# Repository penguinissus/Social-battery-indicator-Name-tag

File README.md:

# Social battery indicator Name tag

Schematic Screenshot:  
  
PCB Screenshot:  
  
3D View:  

# Description
I took the idea of making a name tag and added lights as a social battery indicator  
The three lights will be red yellow and green respectively  
The 18 transistors are supposed to be 3 SR flip flops and 3 or gates  
Heres a logic diagram  

# Bill of Materials  
1 Battery Holder  
3 LEDs  
3 Push Buttons  
6 PNP Transistors  
12 NPN Transistors  
1 10k Resistor  
9 1k Resistors  
3 220 Resistors  
  
Slack username: @penguinissus

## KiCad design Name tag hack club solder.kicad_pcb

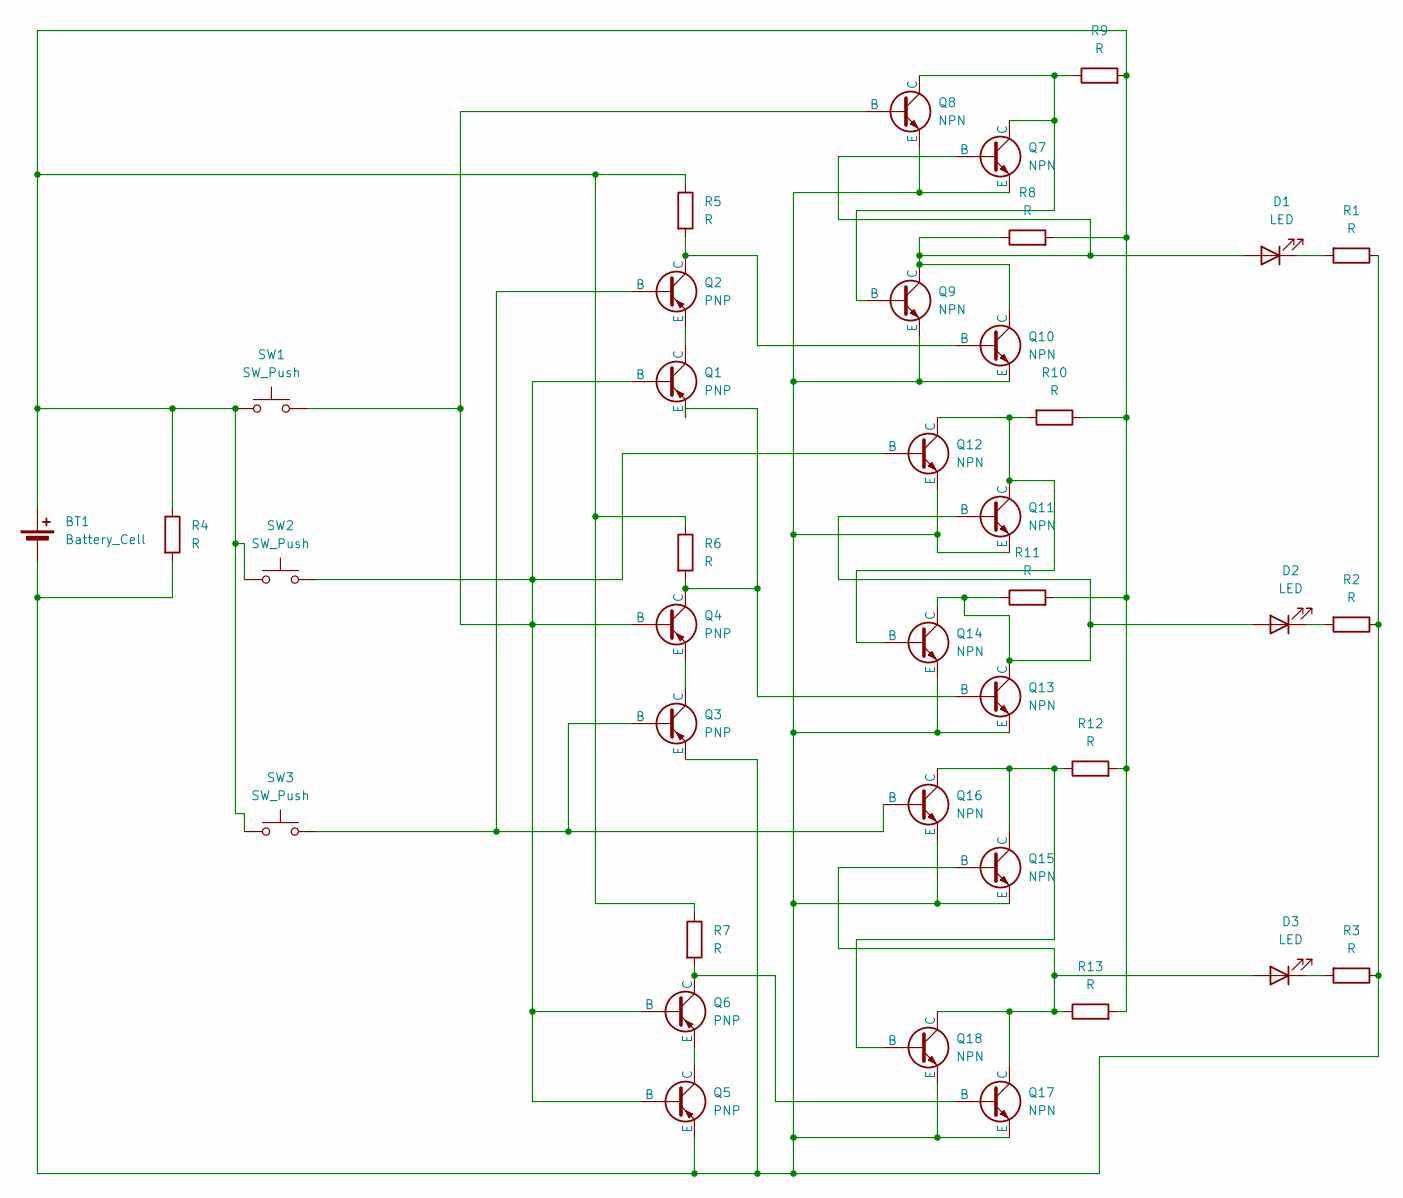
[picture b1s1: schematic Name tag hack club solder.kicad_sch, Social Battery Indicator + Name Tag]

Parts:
BT1: Battery_Cell; BatteryHolder_Keystone_3034_1x20mm
D1, D2, D3: LED; LED_D5.0mm
Q1, Q2, Q3, Q4, Q5, Q6: PNP; TO-92L_HandSolder
Q7, Q8, Q9, Q10, Q11, Q12, Q13, Q14, Q15, Q16, Q17, Q18: NPN; TO-92L_HandSolder
R1, R2, R3, R4, R5, R6, R7, R8, R9, R10, R11, R12, R13: R; R_Axial_DIN0207_L6.3mm_D2.5mm_P7.62mm_Horizontal
SW1, SW2, SW3: SW_Push; SW_PUSH_6mm

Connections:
unnamed: BT1.1 (+), R4.1, R5.1, R6.1, R7.1, R8.2, R9.2, R10.1, R11.2, R12.2, R13.2, SW1.1, SW2.1, SW3.1
unnamed: BT1.2 (-), Q3.3 (E), Q5.3 (E), Q7.3 (E), Q8.3 (E), Q9.3 (E), Q10.3 (E), Q11.3 (E), Q12.3 (E), Q13.3 (E), Q14.3 (E), Q15.3 (E), Q16.3 (E), Q17.3 (E), Q18.3 (E), R1.1, R2.1, R3.1, R4.2
unnamed: D1.2 (A), Q7.2 (B), Q9.1 (C), Q10.1 (C), R8.1
unnamed: D1.1 (K), R1.2
unnamed: D2.2 (A), Q11.2 (B), Q13.1 (C), Q14.1 (C), R11.1
unnamed: D2.1 (K), R2.2
unnamed: D3.2 (A), Q15.2 (B), Q17.1 (C), Q18.1 (C), R13.1
unnamed: D3.1 (K), R3.2
unnamed: Q1.2 (B), Q4.2 (B), Q5.2 (B), Q6.2 (B), Q8.2 (B), Q12.2 (B), SW1.2, SW2.2
unnamed: Q1.1 (C), Q2.3 (E)
unnamed: Q1.3 (E), Q4.1 (C), Q13.2 (B), R6.2
unnamed: Q3.1 (C), Q4.3 (E)
unnamed: Q5.1 (C), Q6.3 (E)
unnamed: Q7.1 (C), Q8.1 (C), Q9.2 (B), R9.1
unnamed: Q2.1 (C), Q10.2 (B), R5.2
unnamed: Q11.1 (C), Q12.1 (C), Q14.2 (B), R10.2
unnamed: Q15.1 (C), Q16.1 (C), Q18.2 (B), R12.1
unnamed: Q2.2 (B), Q3.2 (B), Q16.2 (B), SW3.2
unnamed: Q6.1 (C), Q17.2 (B), R7.2

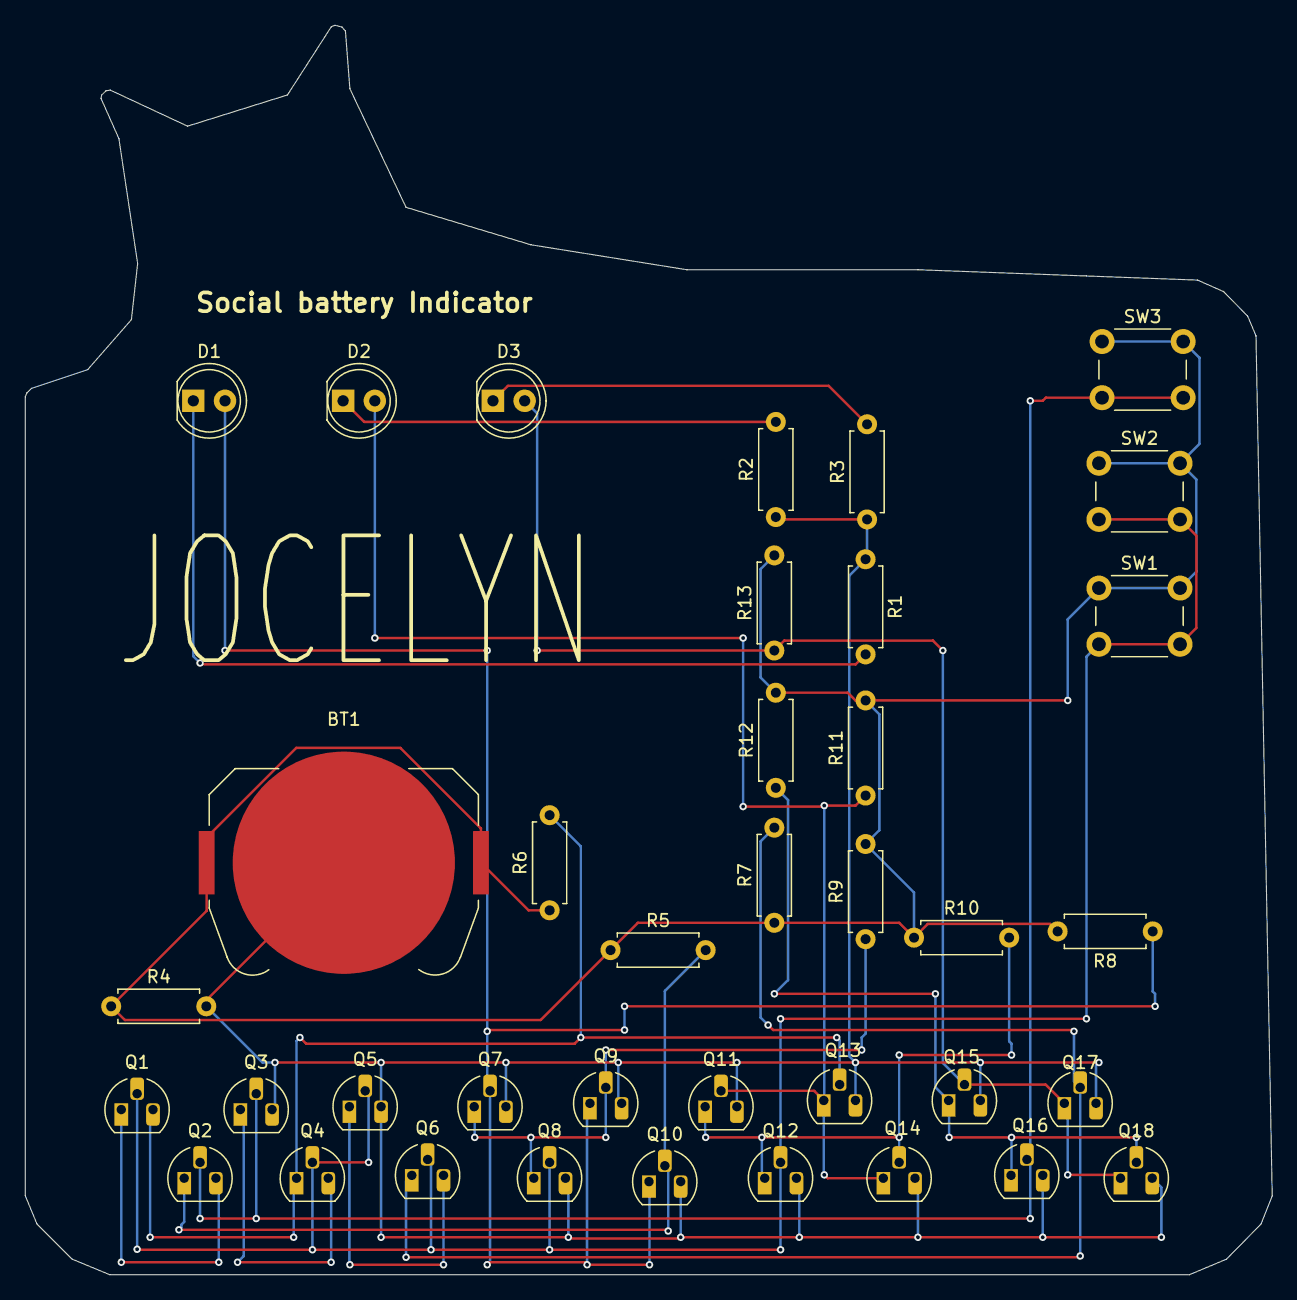
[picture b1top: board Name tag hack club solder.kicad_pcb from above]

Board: 2 copper layers, 99.9 x 100.1 mm, 38 parts (0 on the bottom side), 19 nets.

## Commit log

2025-04-25 Added files
